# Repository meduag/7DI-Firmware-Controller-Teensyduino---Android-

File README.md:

# 7DI-Firmware-Controller-Teensyduino---Android-
Proyecto de desarrollo de un controlador de un dispositivo de estimulación eléctrica, basado en Android y arduino via Bluetooth

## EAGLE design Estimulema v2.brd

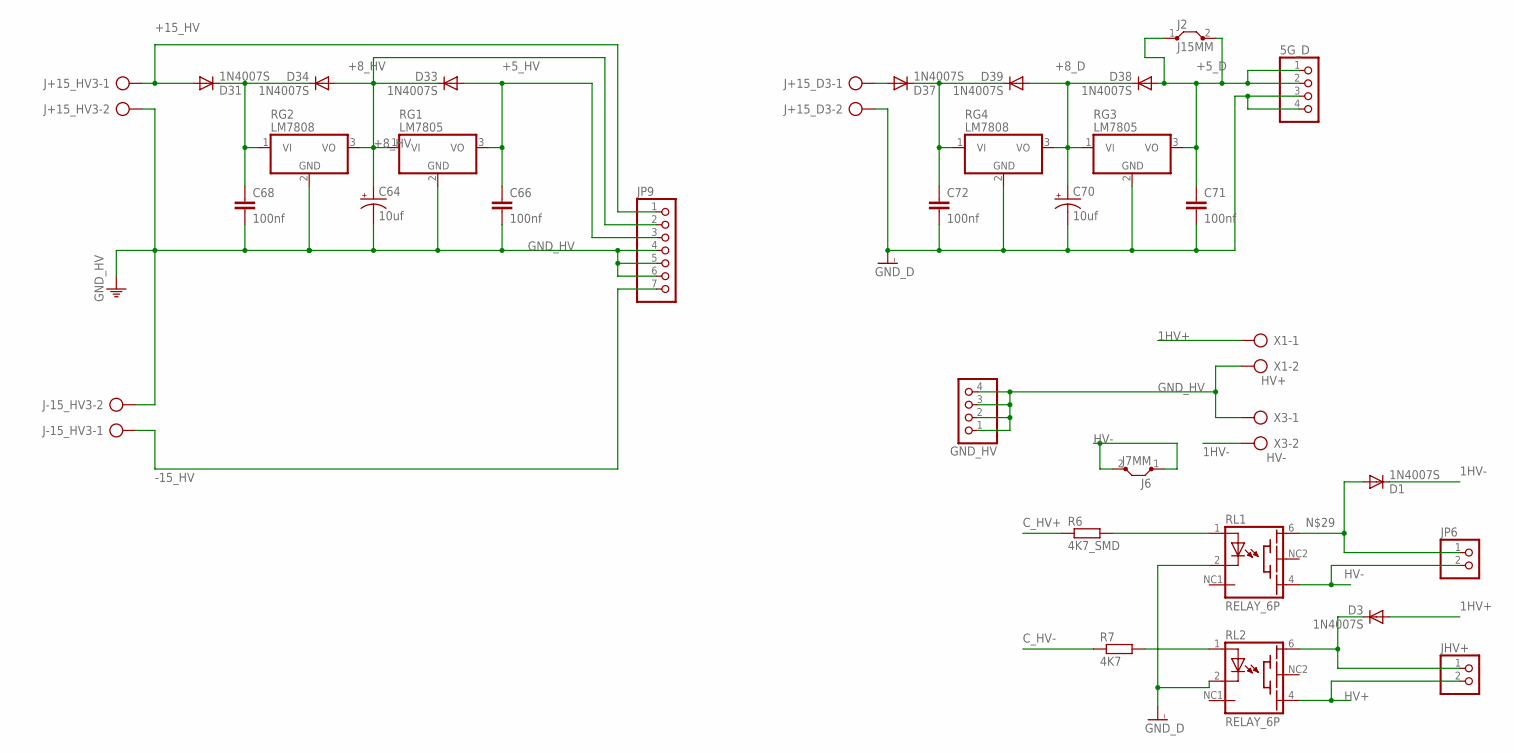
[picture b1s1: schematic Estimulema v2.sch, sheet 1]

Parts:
5G_D: PINHD-1X4; 1X04
C64, C70: 10uf; E2-5
C66, C68, C71, C72: 100nf; C025-024X044
D1, D3, D31, D33, D34, D37, D38, D39: 1N4007S; DIODO4MM
GND_HV: PINHD-1X4; 1X04
J2: J15MM; 15
J6: J7MM; 07
J+15_D3, J+15_HV3: AK300/2
J-15_HV3: AK300/2
JHV+: PINHD-1X2; 1X02
JP6: PINHD-1X2; 1X02
JP9: PINHD-1X7; 1X07
R6: 4K7_SMD; RESISTENCIA_0805
R7: 4K7; RESISTENCIA_0805
RG1, RG3: LM7805; TO220V
RG2, RG4: LM7808; TO220V
RL1, RL2: RELAY_6P; TS210
X1: HV+; AK300/2
X3: HV-; AK300/2

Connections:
1HV+: D3.A, X1.1
1HV-: D1.C, X3.2
+4: D37.A, J+15_D3.1
+5_D: 5G_D.1, 5G_D.2, C71.1, D38.A, J2.1, J2.2, RG3.3 (VO); also elsewhere on the board
+5_HV: C66.1, D33.A, JP9.3, RG1.3 (VO); also elsewhere on the board
+8_D: C70.+, D38.C, D39.A, RG3.1 (VI), RG4.3 (VO)
+8_HV: C64.+, D33.C, D34.A, JP9.2, RG1.1 (VI), RG2.3 (VO)
+15_HV: D31.A, J+15_HV3.1, JP9.1; also elsewhere on the board
-15_HV: J-15_HV3.1, JP9.7; also elsewhere on the board
C_HV+: R6.1; also elsewhere on the board
C_HV-: R7.1; also elsewhere on the board
GND_D: 5G_D.3, 5G_D.4, C70.-, C71.2, C72.2, J+15_D3.2, RG3.2 (GND), RG4.2 (GND), RL1.2 (C), RL2.2 (C); also elsewhere on the board
GND_HV: C64.-, C66.2, C68.2, GND_HV.1, GND_HV.2, GND_HV.3, GND_HV.4, J+15_HV3.2, J-15_HV3.2, JP9.4, JP9.5, JP9.6, RG1.2 (GND), RG2.2 (GND), X1.2, X3.1; also elsewhere on the board
HV+: JHV+.2, RL2.4 (EMI); also elsewhere on the board
HV-: J6.1, J6.2, JP6.2, RL1.4 (EMI); also elsewhere on the board
unnamed: R6.2, RL1.1 (A)
unnamed: R7.2, RL2.1 (A)
unnamed: D1.A, JP6.1, RL1.6 (BAS)
unnamed: D3.C, JHV+.1, RL2.6 (BAS)
unnamed: C68.1, D31.C, D34.C, RG2.1 (VI)
unnamed: C72.1, D37.C, D39.C, RG4.1 (VI)

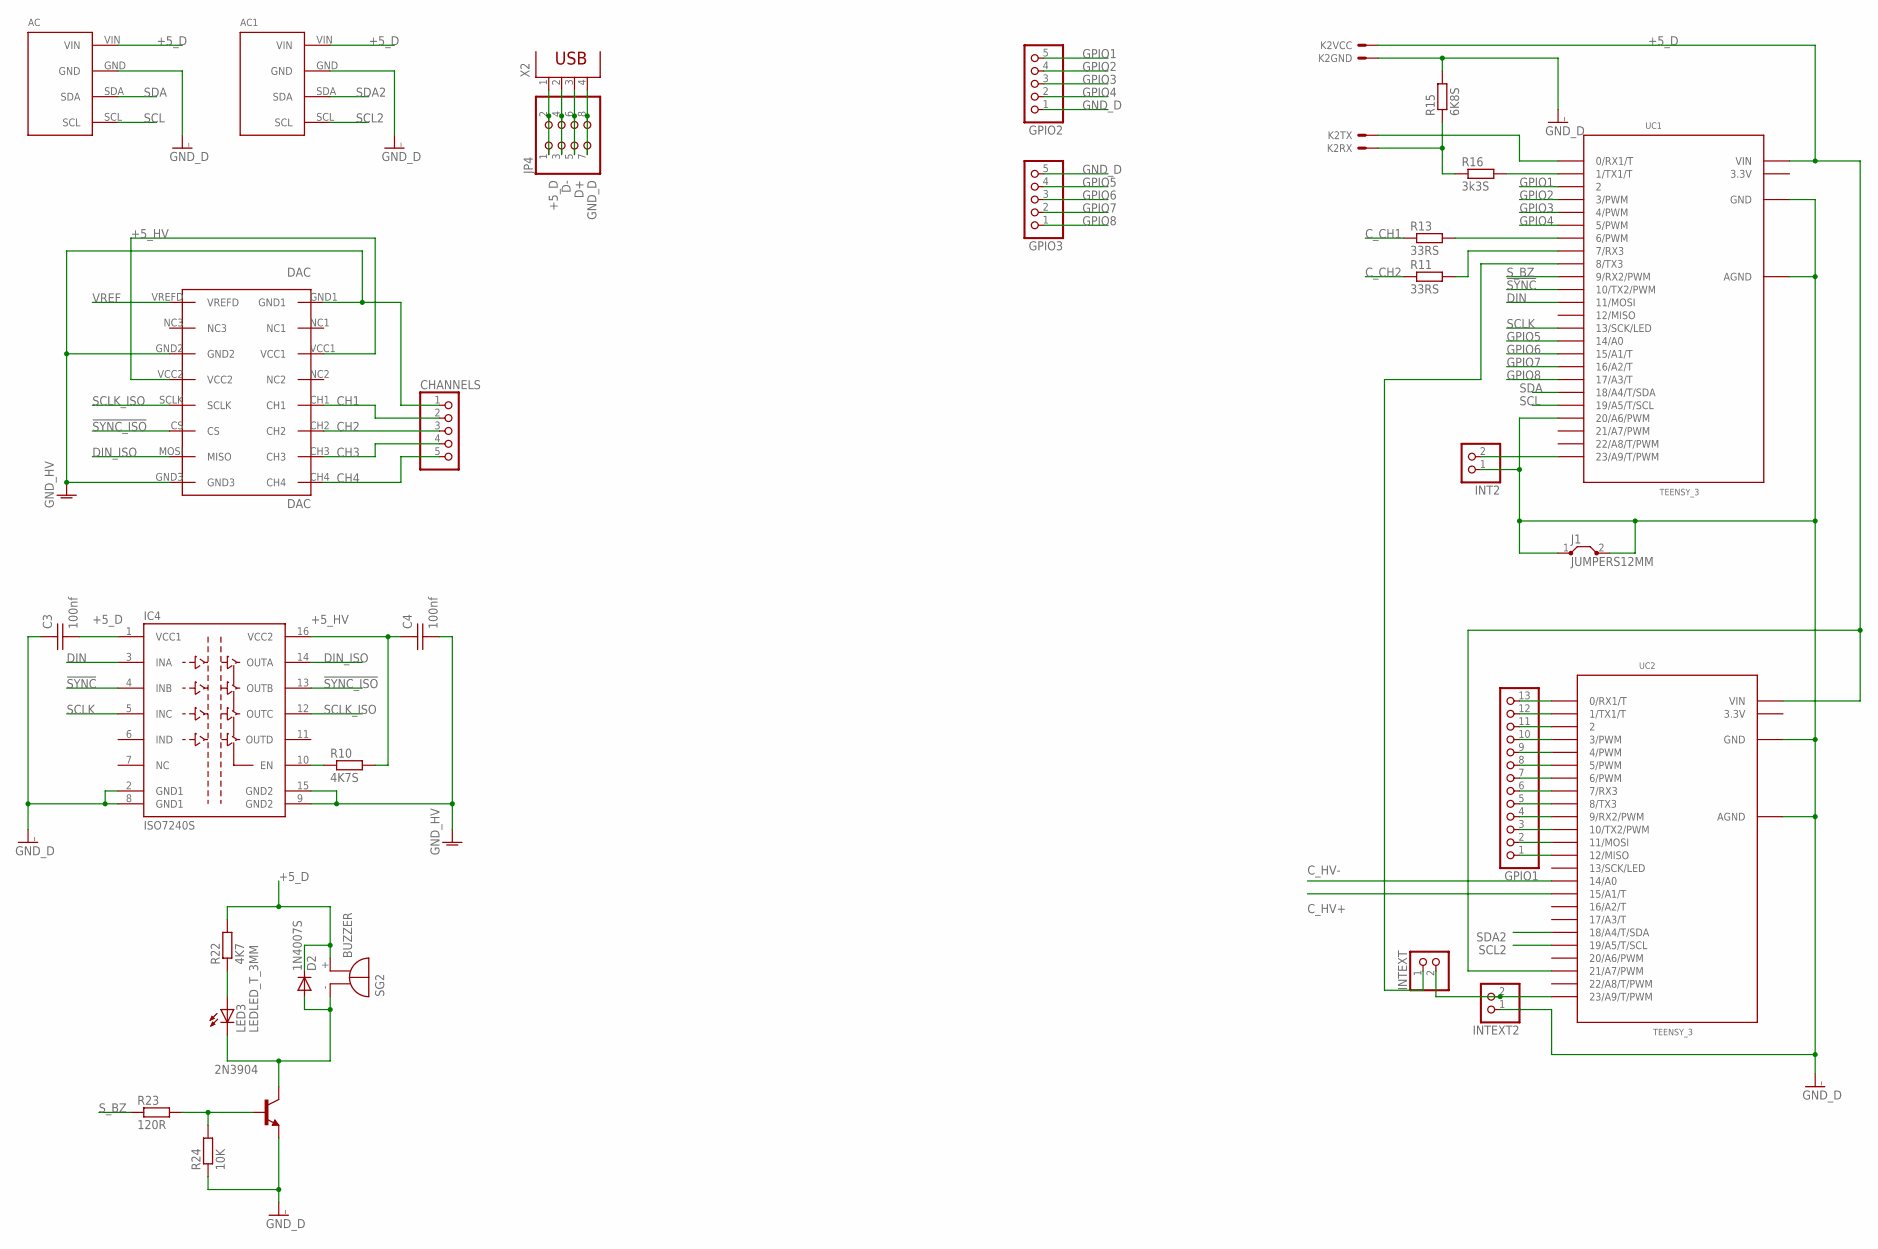
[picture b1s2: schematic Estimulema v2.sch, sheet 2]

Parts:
2N3904: 29-NPN-TO92-EBC; TO92-EBC
AC: CONECTOR_ACELEROMETRO_MPU6050CONECTOR_MPU6050; MPU6050
AC1: MPU6050
C3, C4: 100nf; CAP_CER_SMD-0805
CHANNELS: PINHD-1X5; 1X05
D2: 1N4007S; DIODO4MM
DAC: DAC; DACMOD_P
GPIO1: PINHD-1X13; 1X13
GPIO2, GPIO3: PINHD-1X5; 1X05
IC4: ISO7240S; SO-16DW
INT2: PINHD-1X2; 1X02
INTEXT, INTEXT2: PINHD-1X2; 1X02
J1: JUMPERS12MM; 12
JP4: PINHD-2X4; 2X04
K2: HC-06; CONECTOR_BTHC-06
LED3: LEDLED_T_3MM; LED3MM
R10: 4K7S; RESISTENCIA_0805
R11, R13: 33RS; RESISTENCIA_0805
R15: 6K8S; RESISTENCIA_0805
R16: 3k3S; RESISTENCIA_0805
R22: 4K7; RESISTENCIA_0805
R23: 120R; RESISTENCIA_0805
R24: 10K; RESISTENCIA_0805
SG2: BUZZER
UC1, UC2: TEENSY_3; TEENSY_3.0-3.2_DIL
X2: PN61729

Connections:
3.3V: UC1.3.3V, UC2.3.3V
!SYNC: IC4.4 (INB), UC1.10 (10/TX2/PWM)
!SYNC_ISO: DAC.CS, IC4.13 (OUTB)
+5_D: AC.VIN, AC1.VIN, C3.2, D2.C, IC4.1 (VCC1), JP4.1, JP4.2, K2.1, R22.2, SG2.+ (-), UC1.VIN, UC2.21/A7 (21/A7/PWM), UC2.VIN, X2.1; also elsewhere on the board
+5_HV: C4.1, DAC.VCC1, DAC.VCC2, IC4.16 (VCC2), R10.2; also elsewhere on the board
CH1: CHANNELS.2, DAC.CH1; also elsewhere on the board
CH2: CHANNELS.3, DAC.CH2; also elsewhere on the board
CH3: CHANNELS.4, DAC.CH3
CH4: CHANNELS.5, DAC.CH4
C_CH1: R13.1; also elsewhere on the board
C_CH2: R11.1; also elsewhere on the board
C_HV+: UC2.15/A1 (15/A1/T); also elsewhere on the board
C_HV-: UC2.14/A0; also elsewhere on the board
D+: JP4.5, JP4.6, X2.3
D-: JP4.3, JP4.4, X2.2
DIN: IC4.3 (INA), UC1.11 (11/MOSI)
DIN_ISO: DAC.MOSI (MISO), IC4.14 (OUTA)
GNDI: C3.1, IC4.2 (GND1), IC4.8 (GND1)
GND_D: 2N3904.E, AC.GND, AC1.GND, GPIO2.1, GPIO3.5, INT2.1, INTEXT2.1, J1.1, J1.2, JP4.7, JP4.8, K2.2, R15.2, R24.1, UC1.20/A6 (20/A6/PWM), UC1.AGND, UC1.GND, UC2.AGND, UC2.GND, X2.4; also elsewhere on the board
GND_HV: C4.2, CHANNELS.1, DAC.GND1, DAC.GND2, DAC.GND3, IC4.9 (GND2), IC4.15 (GND2); also elsewhere on the board
GPIO1: GPIO2.5, UC1.2
GPIO2: GPIO2.4, UC1.3 (3/PWM)
GPIO3: GPIO2.3, UC1.4 (4/PWM)
GPIO4: GPIO2.2, UC1.5 (5/PWM)
GPIO5: GPIO3.4, UC1.14/A0
GPIO6: GPIO3.3, UC1.15/A1 (15/A1/T)
GPIO7: GPIO3.2, UC1.16/A2 (16/A2/T)
GPIO8: GPIO3.1, UC1.17/A3 (17/A3/T)
unnamed: INTEXT.2, INTEXT2.2, UC2.23/A9 (23/A9/T/PWM)
unnamed: INTEXT.1, UC1.8 (8/TX3)
unnamed: GPIO1.13, UC2.0 (0/RX1/T)
unnamed: GPIO1.12, UC2.1 (1/TX1/T)
unnamed: GPIO1.11, UC2.2
unnamed: GPIO1.10, UC2.3 (3/PWM)
unnamed: GPIO1.9, UC2.4 (4/PWM)
unnamed: GPIO1.8, UC2.5 (5/PWM)
unnamed: GPIO1.7, UC2.6 (6/PWM)
unnamed: GPIO1.6, UC2.7 (7/RX3)
unnamed: GPIO1.5, UC2.8 (8/TX3)
unnamed: GPIO1.4, UC2.9 (9/RX2/PWM)
unnamed: GPIO1.3, UC2.10 (10/TX2/PWM)
unnamed: GPIO1.2, UC2.11 (11/MOSI)
unnamed: GPIO1.1, UC2.12 (12/MISO)
unnamed: IC4.10 (EN), R10.1
unnamed: R13.2, UC1.6 (6/PWM)
unnamed: R11.2, UC1.7 (7/RX3)
unnamed: K2.4, R15.1, R16.1
unnamed: R16.2, UC1.1 (1/TX1/T)
unnamed: K2.3, UC1.0 (0/RX1/T)
unnamed: LED3.A, R22.1
unnamed: 2N3904.C, D2.A, LED3.K (C), SG2.- (+)
unnamed: 2N3904.B, R23.2, R24.2
unnamed: INT2.2, UC1.23/A9 (23/A9/T/PWM)
SCL: AC.SCL, UC1.19/A5 (19/A5/T/SCL)
SCL2: AC1.SCL, UC2.19/A5 (19/A5/T/SCL)
SCLK: IC4.5 (INC), UC1.13 (13/SCK/LED)
SCLK_ISO: DAC.SCLK, IC4.12 (OUTC)
SDA: AC.SDA, UC1.18/A4 (18/A4/T/SDA)
SDA2: AC1.SDA, UC2.18/A4 (18/A4/T/SDA)
S_BZ: R23.1, UC1.9 (9/RX2/PWM)
VREF: DAC.VREFD; also elsewhere on the board

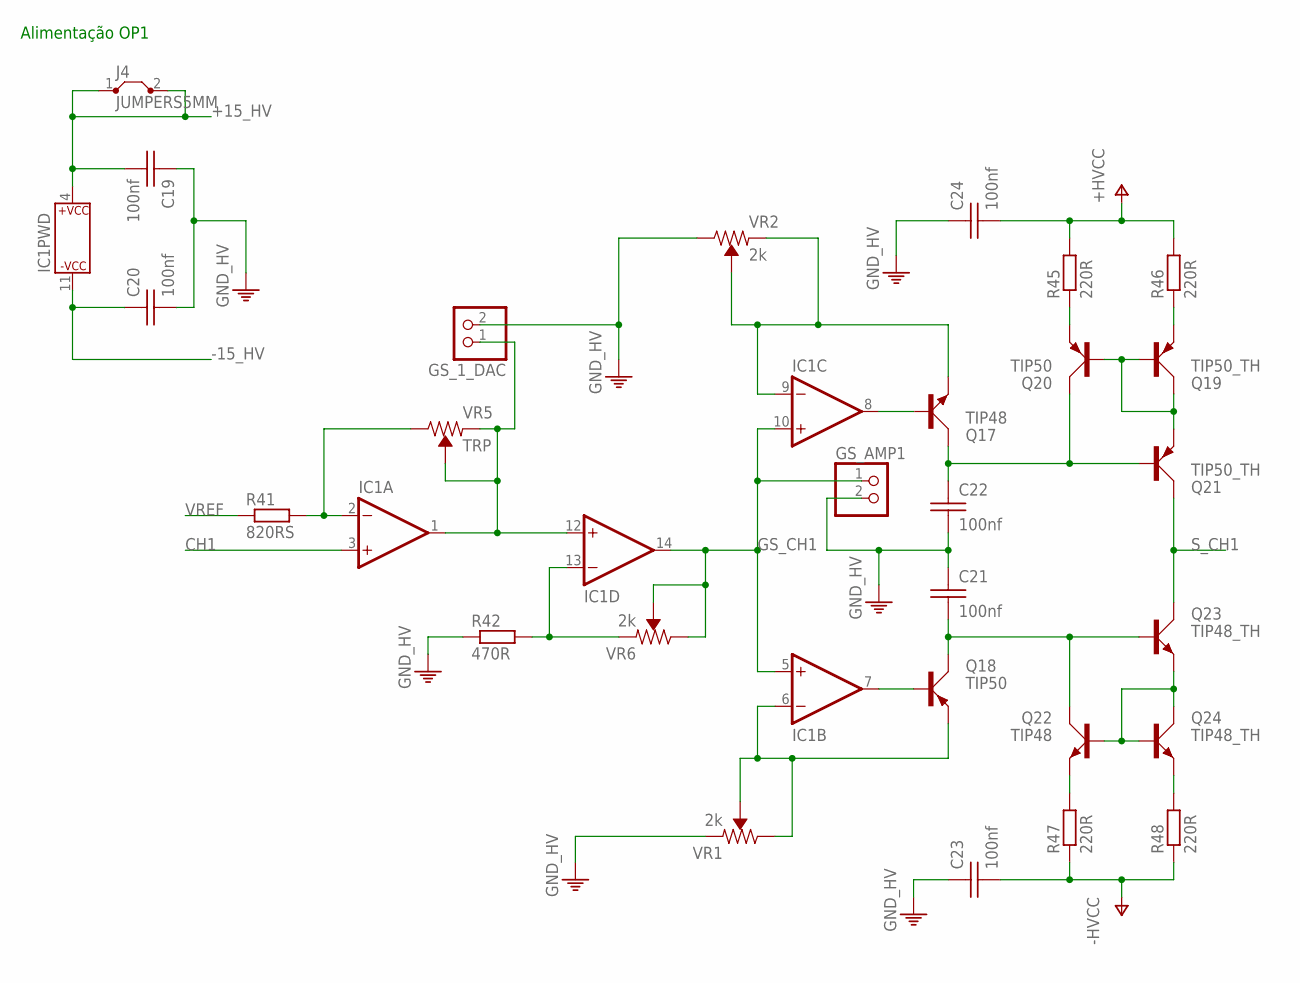
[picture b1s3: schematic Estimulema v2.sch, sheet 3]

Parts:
C19, C20: 100nf; CAP_CER_SMD-0805
C21, C22: 100nf; CAP_CER_2,54-5X5
C23, C24: 100nf; CAP_CER_16X7
GS_1_DAC: PINHD-1X2; 1X02
GS_AMP1: PINHD-1X2; 1X02
IC1: TL084; DIL14
J4: JUMPERS5MM; 05
Q17, Q22: TIP48; TO220
Q18, Q20: TIP50; TO220
Q19, Q21: TIP50_TH; TO220
Q23, Q24: TIP48_TH; TO220
R41: 820RS; RESISTENCIA_0805
R42: 470R; RESISTENCIA_0805
R45, R46, R47, R48: 220R; 0204V
VR1, VR2, VR6: 2k; TRIMPOT-PTH-3386U
VR5: TRP; TRIMPOT-PTH-3386U

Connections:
+15_HV: C19.2, IC1.4 (P$V+), J4.1, J4.2; also elsewhere on the board
-15_HV: C20.1, IC1.11 (P$V-); also elsewhere on the board
CH1: IC1.3 (+IN); also elsewhere on the board
GND_HV: C19.1, C20.2, C21.1, C22.2, C23.1, C24.1, GS_1_DAC.2, GS_AMP1.2, R42.1, VR1.1 (CCW), VR2.3 (CW); also elsewhere on the board
GS_CH1: GS_AMP1.1, IC1.5 (+IN), IC1.10 (+IN), IC1.14 (OUT), VR6.2 (WIPER), VR6.3 (CW)
HV+: C24.2, R45.2, R46.2; also elsewhere on the board
HV-: C23.2, R47.1, R48.1; also elsewhere on the board
unnamed: IC1.2 (-IN), R41.2, VR5.3 (CW)
unnamed: GS_1_DAC.1, IC1.1 (OUT), IC1.12 (+IN), VR5.1 (CCW), VR5.2 (WIPER)
unnamed: IC1.13 (-IN), R42.2, VR6.1 (CCW)
unnamed: IC1.9 (-IN), Q17.E, VR2.1 (CCW), VR2.2 (WIPER)
unnamed: IC1.6 (-IN), Q18.E, VR1.2 (WIPER), VR1.3 (CW)
unnamed: C21.2, Q18.C, Q22.C, Q23.B
unnamed: C22.1, Q17.C, Q20.C, Q21.B
unnamed: Q20.E, R45.1
unnamed: Q19.E, R46.1
unnamed: Q19.B, Q19.C, Q20.B, Q21.E
unnamed: Q22.B, Q23.E, Q24.B, Q24.C
unnamed: Q22.E, R47.2
unnamed: Q24.E, R48.2
unnamed: IC1.8 (OUT), Q17.B
unnamed: IC1.7 (OUT), Q18.B
S_CH1: Q21.C, Q23.C; also elsewhere on the board
VREF: R41.1; also elsewhere on the board

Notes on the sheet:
Alimentação OP1

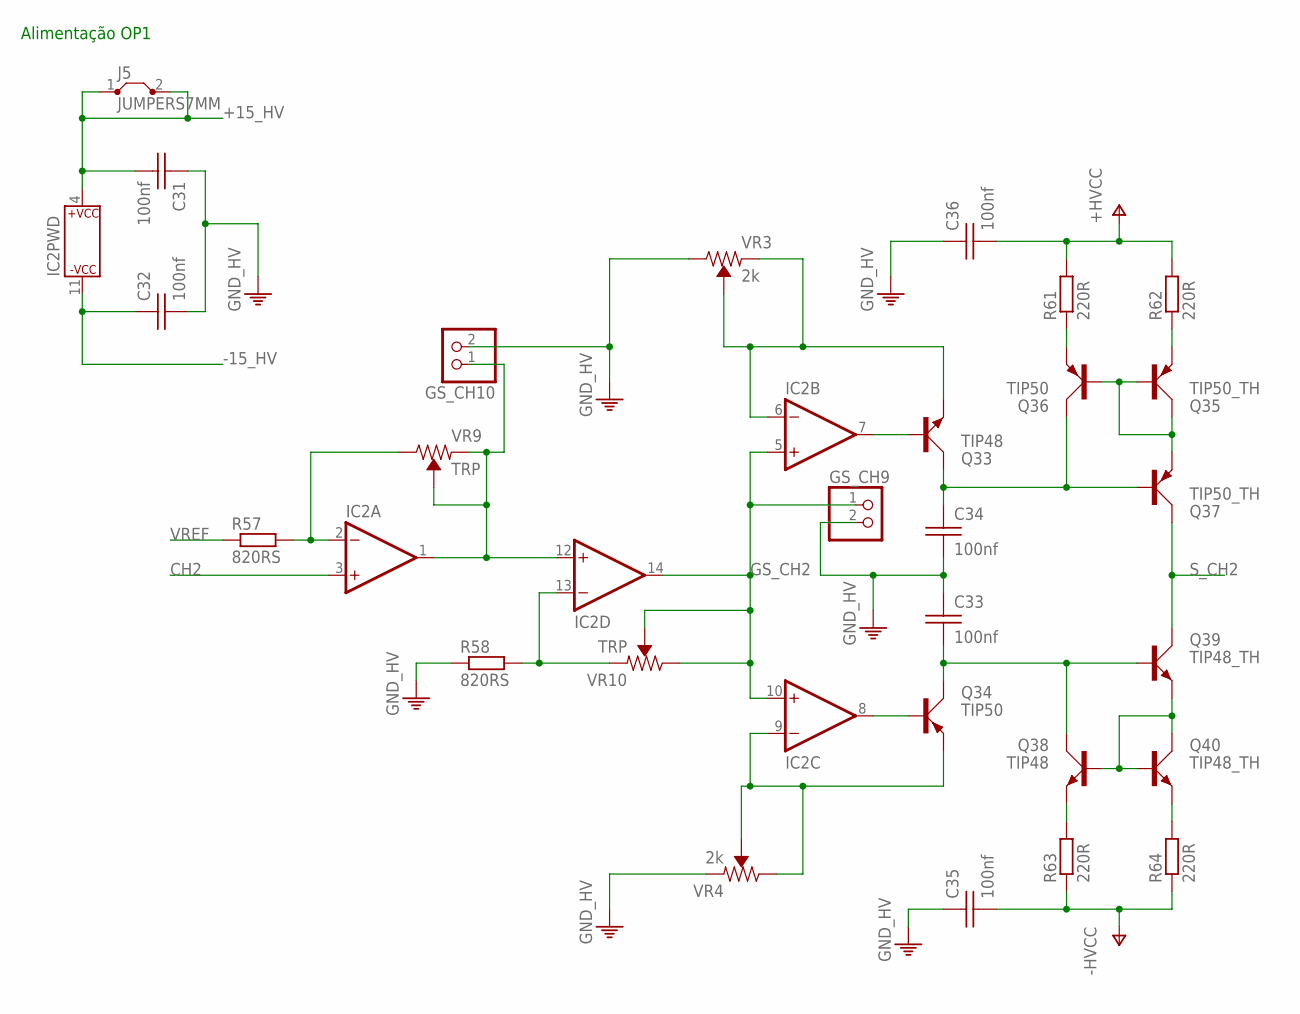
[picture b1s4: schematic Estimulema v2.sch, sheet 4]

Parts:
C31, C32: 100nf; CAP_CER_SMD-0805
C33, C34: 100nf; CAP_CER_2,54-5X5
C35, C36: 100nf; CAP_CER_16X7
GS_CH9, GS_CH10: PINHD-1X2; 1X02
IC2: TL084; DIL14
J5: JUMPERS7MM; 07
Q33, Q38: TIP48; TO220
Q34, Q36: TIP50; TO220
Q35, Q37: TIP50_TH; TO220
Q39, Q40: TIP48_TH; TO220
R57, R58: 820RS; RESISTENCIA_0805
R61, R62, R63, R64: 220R; 0204V
VR3, VR4: 2k; TRIMPOT-PTH-3386U
VR9, VR10: TRP; TRIMPOT-PTH-3386U

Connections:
+15_HV: C31.2, IC2.4 (P$V+), J5.1, J5.2; also elsewhere on the board
-15_HV: C32.1, IC2.11 (P$V-); also elsewhere on the board
CH2: IC2.3 (+IN); also elsewhere on the board
GND_HV: C31.1, C32.2, C33.1, C34.2, C35.1, C36.1, GS_CH9.2, GS_CH10.2, R58.1, VR3.3 (CW), VR4.1 (CCW); also elsewhere on the board
GS_CH2: GS_CH9.1, IC2.5 (+IN), IC2.10 (+IN), IC2.14 (OUT), VR10.2 (WIPER), VR10.3 (CW)
HV+: C36.2, R61.2, R62.2; also elsewhere on the board
HV-: C35.2, R63.1, R64.1; also elsewhere on the board
unnamed: IC2.2 (-IN), R57.2, VR9.3 (CW)
unnamed: GS_CH10.1, IC2.1 (OUT), IC2.12 (+IN), VR9.1 (CCW), VR9.2 (WIPER)
unnamed: IC2.13 (-IN), R58.2, VR10.1 (CCW)
unnamed: IC2.6 (-IN), Q33.E, VR3.1 (CCW), VR3.2 (WIPER)
unnamed: IC2.9 (-IN), Q34.E, VR4.2 (WIPER), VR4.3 (CW)
unnamed: C33.2, Q34.C, Q38.C, Q39.B
unnamed: C34.1, Q33.C, Q36.C, Q37.B
unnamed: Q36.E, R61.1
unnamed: Q35.E, R62.1
unnamed: Q35.B, Q35.C, Q36.B, Q37.E
unnamed: Q38.B, Q39.E, Q40.B, Q40.C
unnamed: Q38.E, R63.2
unnamed: Q40.E, R64.2
unnamed: IC2.7 (OUT), Q33.B
unnamed: IC2.8 (OUT), Q34.B
S_CH2: Q37.C, Q39.C; also elsewhere on the board
VREF: R57.1; also elsewhere on the board

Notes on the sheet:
Alimentação OP1

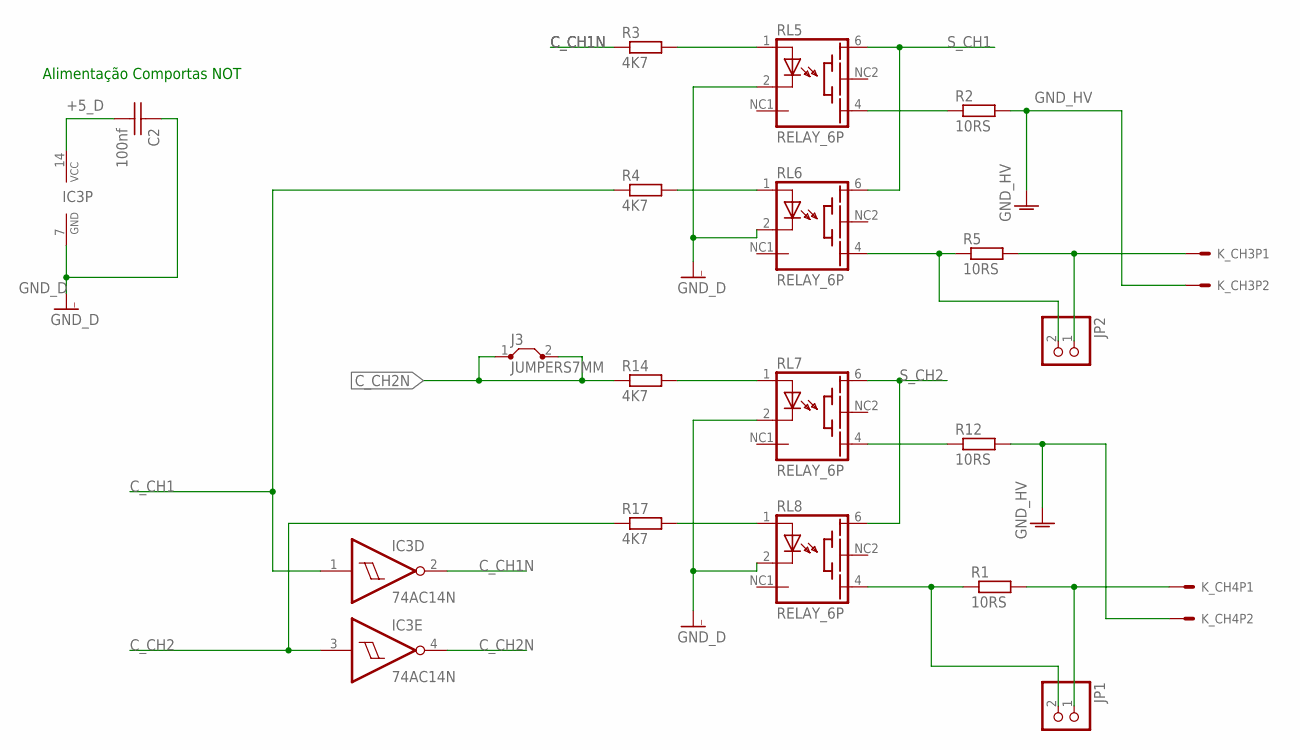
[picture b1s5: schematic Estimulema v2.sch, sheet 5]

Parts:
C2: 100nf; CAP_CER_SMD-0805
IC3: 74AC14N; DIL14
J3: JUMPERS7MM; 07
JP1, JP2: PINHD-1X2; 1X02
K_CH3, K_CH4: CONECTOR_5.08; CONECTOR_X2_5.08
R1, R5: 10RS; 0204/5
R2, R12: 10RS; 0617V
R3, R4, R14, R17: 4K7; RESISTENCIA_0805
RL5, RL6, RL7, RL8: RELAY_6P; TS210

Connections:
+5_D: C2.2, IC3.14 (VCC); also elsewhere on the board
C_CH1: IC3.1 (I), R4.1; also elsewhere on the board
C_CH1N: IC3.2 (O), R3.1
C_CH2: IC3.3 (I), R17.1; also elsewhere on the board
C_CH2N: IC3.4 (O), J3.1, J3.2, R14.1
GND_D: C2.1, IC3.7 (GND), RL5.2 (C), RL6.2 (C), RL7.2 (C), RL8.2 (C); also elsewhere on the board
GND_HV: K_CH3.2, K_CH4.2, R2.2, R12.2; also elsewhere on the board
unnamed: R3.2, RL5.1 (A)
unnamed: R4.2, RL6.1 (A)
unnamed: R2.1, RL5.4 (EMI)
unnamed: JP2.2, R5.1, RL6.4 (EMI)
unnamed: R14.2, RL7.1 (A)
unnamed: R17.2, RL8.1 (A)
unnamed: R12.1, RL7.4 (EMI)
unnamed: JP2.1, K_CH3.1, R5.2
unnamed: JP1.1, K_CH4.1, R1.2
unnamed: JP1.2, R1.1, RL8.4 (EMI)
S_CH1: RL5.6 (BAS), RL6.6 (BAS); also elsewhere on the board
S_CH2: RL7.6 (BAS), RL8.6 (BAS); also elsewhere on the board

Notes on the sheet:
Alimentação Comportas NOT

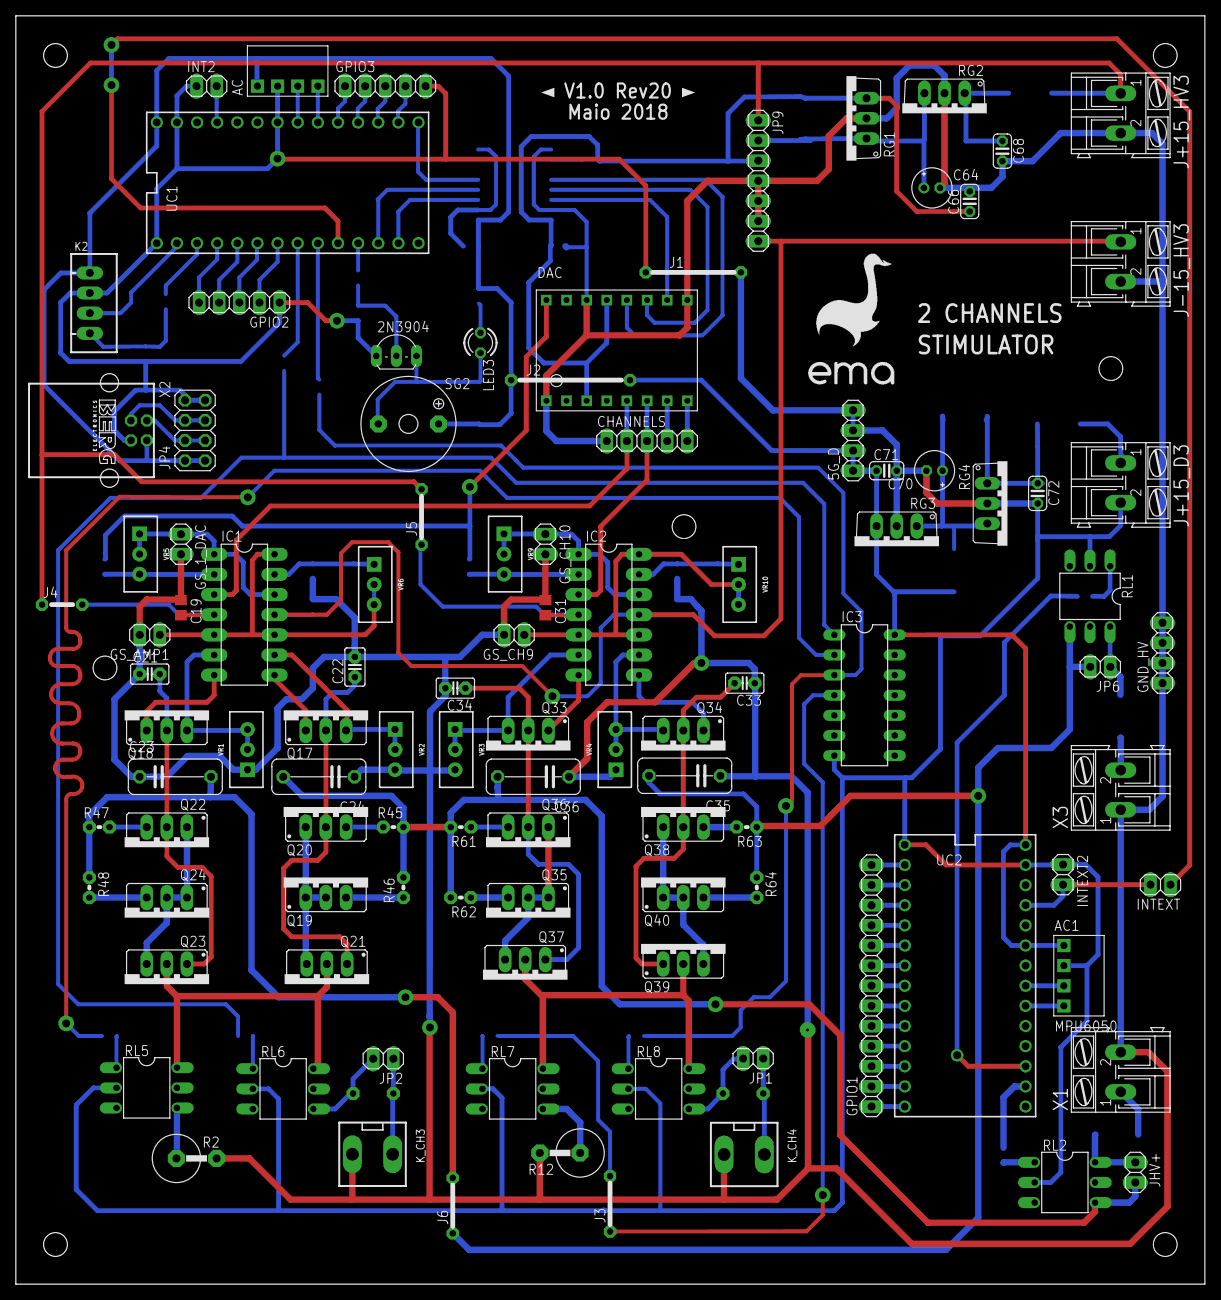
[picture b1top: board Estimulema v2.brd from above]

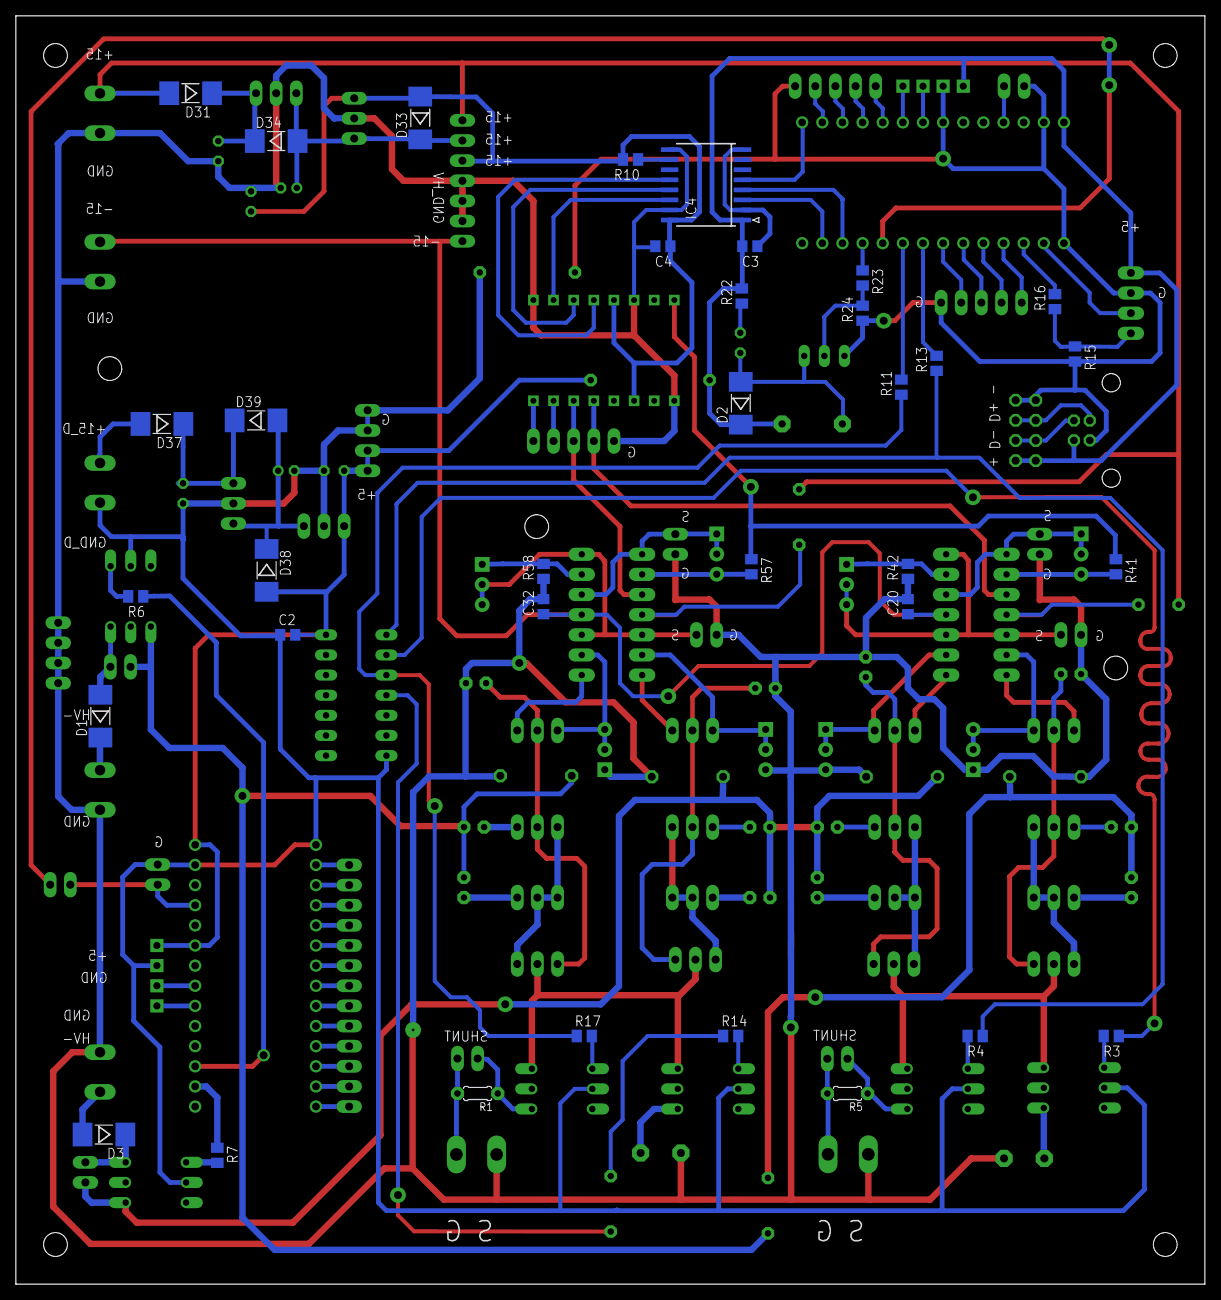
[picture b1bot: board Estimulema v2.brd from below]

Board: 2 copper layers, 150.0 x 160.0 mm, 140 parts (35 on the bottom side), 122 nets.

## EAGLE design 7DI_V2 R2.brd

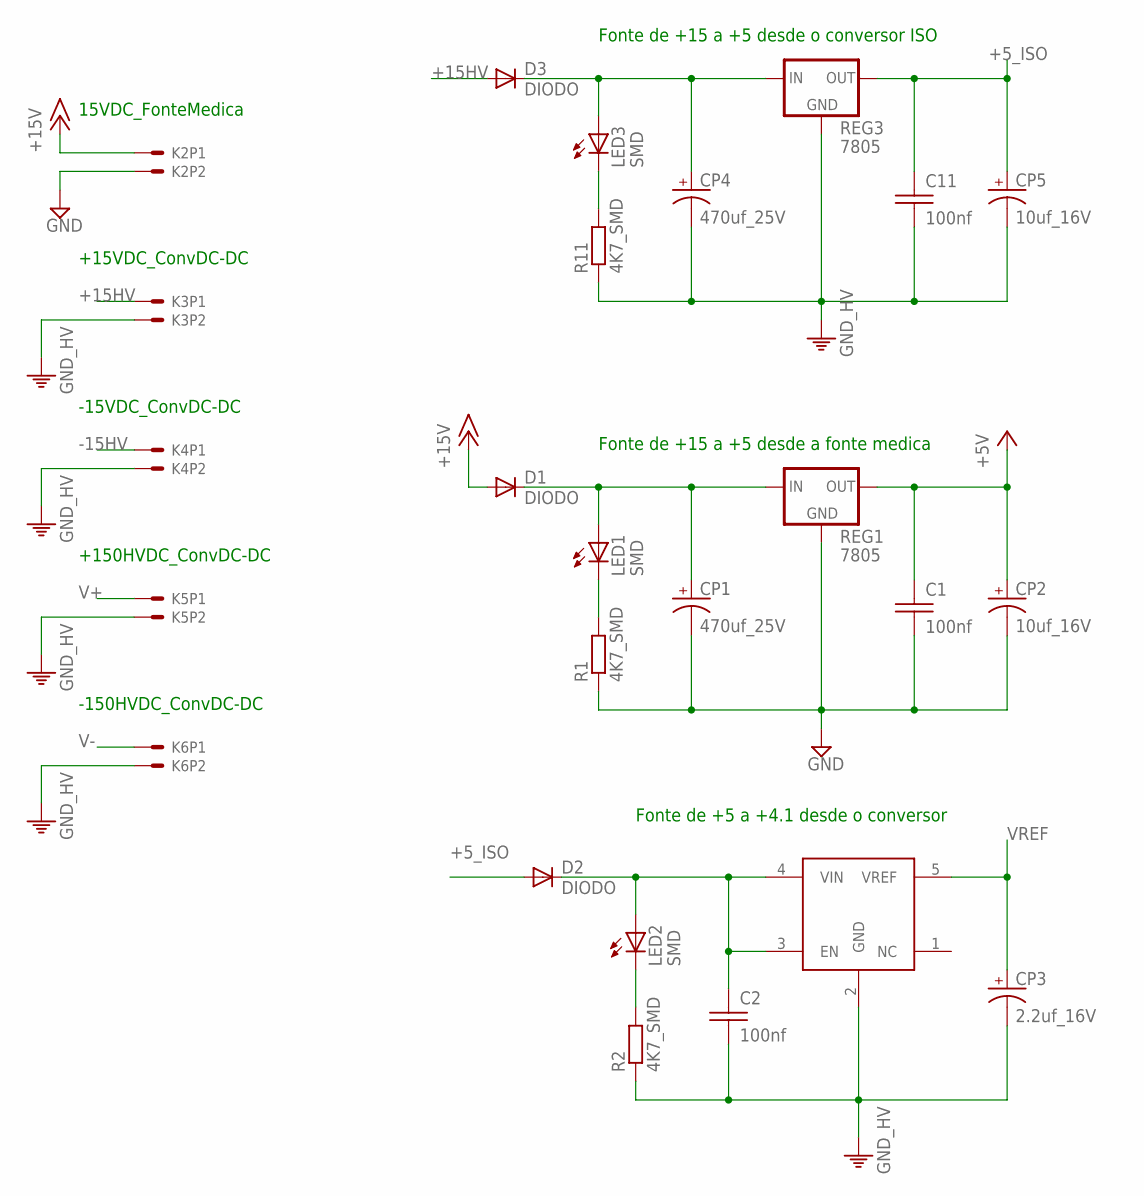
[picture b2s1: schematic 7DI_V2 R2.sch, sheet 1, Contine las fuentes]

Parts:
C1, C11: 100nf; CAP_CER_5,08-024X044
C2: 100nf; CAP_CER_SMD-0805
CP1, CP4: 470uf_25V; CAP_T_3,5-D8
CP2, CP5: 10uf_16V; CAP_T_2,5-D5
CP3: 2.2uf_16V; 153CLV-0605
D1, D2, D3: DIODO; D-5
K2: CONECTOR_5.08; CONECTOR_X2_5.08
K3, K4, K5, K6: vcc; CONECTOR_X2_5.08
LED1, LED2, LED3: SMD; LED_0805
R1, R2, R11: 4K7_SMD; RESISTENCIA_0805
REG1, REG3: 7805; 78XXS
REG2: lm4132_4.1; SOT23

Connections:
+5V: C1.1, CP2.+, REG1.OUT; also elsewhere on the board
+5_ISO: C11.1, CP5.+, D2.A, REG3.OUT; also elsewhere on the board
+15HV: D3.A, K3.1; also elsewhere on the board
+15V: D1.A, K2.1
-15HV: K4.1; also elsewhere on the board
GND: C1.2, CP1.-, CP2.-, K2.2, R1.1, REG1.GND; also elsewhere on the board
unnamed: CP1.+, D1.C, LED1.A, REG1.IN
unnamed: LED1.C, R1.2
unnamed: C2.1, D2.C, LED2.A, REG2.3 (EN), REG2.4 (VIN)
unnamed: LED2.C, R2.2
unnamed: CP4.+, D3.C, LED3.A, REG3.IN
unnamed: LED3.C, R11.2
PE: C2.2, C11.2, CP3.-, CP4.-, CP5.-, K3.2, K4.2, K5.2, K6.2, R2.1, R11.1, REG2.2 (GND), REG3.GND; also elsewhere on the board
V+: K5.1; also elsewhere on the board
V-: K6.1; also elsewhere on the board
VREF: CP3.+, REG2.5 (VREF); also elsewhere on the board

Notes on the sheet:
15VDC_FonteMedica
+15VDC_ConvDC-DC
-15VDC_ConvDC-DC
+150HVDC_ConvDC-DC
-150HVDC_ConvDC-DC
Fonte de +15 a +5 desde o conversor ISO
Fonte de +15 a +5 desde a fonte medica
Fonte de +5 a +4.1 desde o conversor

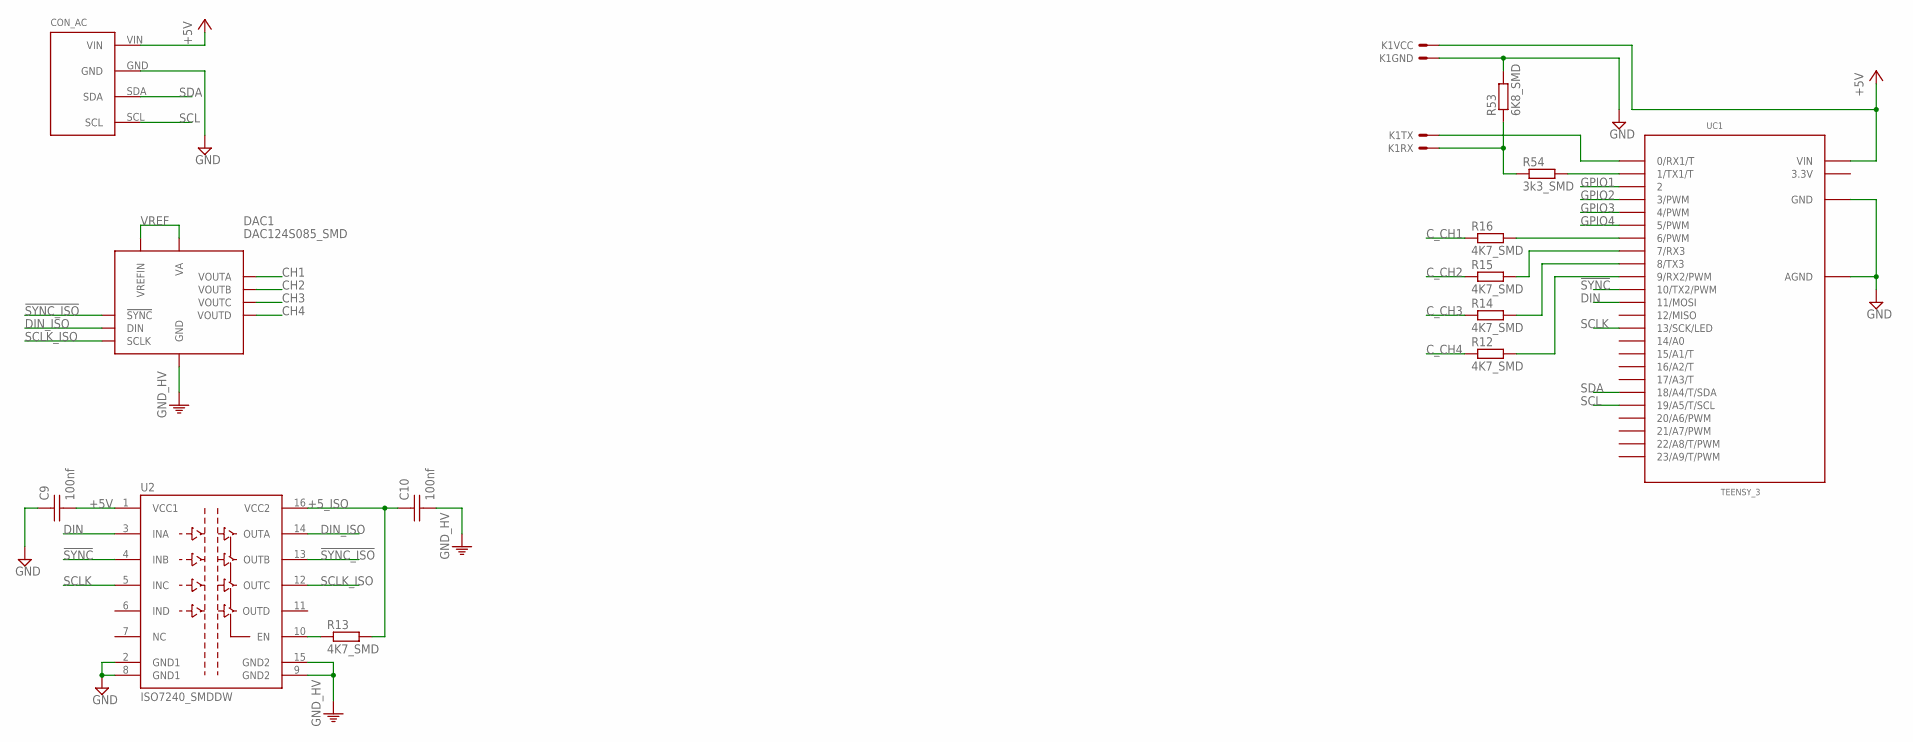
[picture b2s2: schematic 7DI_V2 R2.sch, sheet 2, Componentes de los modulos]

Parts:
C9, C10: 100nf; CAP_CER_SMD-0805
CON_AC: CON_MPU6050; MPU6050
DAC1: DAC124S085_SMD; DAC_SO10
K1: CONECTOR_BTHC-06HC-06; CONECTOR_BTHC-06
R12, R13, R14, R15, R16: 4K7_SMD; RESISTENCIA_0805
R53: 6K8_SMD; RESISTENCIA_0805
R54: 3k3_SMD; RESISTENCIA_0805
U2: ISO7240_SMDDW; SO-16DW
UC1: TEENSY_3; TEENSY_3.0-3.2_DIL

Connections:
3.3V: UC1.3.3V
!SYNC: U2.4 (INB), UC1.10 (10/TX2/PWM)
!SYNC_ISO: DAC1.9 (!SYNC!), U2.13 (OUTB)
+5V: C9.2, CON_AC.VIN, K1.1, U2.1 (VCC1), UC1.VIN; also elsewhere on the board
+5_ISO: C10.1, R13.2, U2.16 (VCC2); also elsewhere on the board
CH1: DAC1.2 (VOUTA); also elsewhere on the board
CH2: DAC1.3 (VOUTB); also elsewhere on the board
CH3: DAC1.4 (VOUTC); also elsewhere on the board
CH4: DAC1.5 (VOUTD); also elsewhere on the board
C_CH1: R16.1; also elsewhere on the board
C_CH2: R15.1; also elsewhere on the board
C_CH3: R14.1; also elsewhere on the board
C_CH4: R12.1; also elsewhere on the board
DIN: U2.3 (INA), UC1.11 (11/MOSI)
DIN_ISO: DAC1.8 (DIN), U2.14 (OUTA)
GND: C9.1, CON_AC.GND, K1.2, R53.2, U2.2 (GND1), U2.8 (GND1), UC1.AGND, UC1.GND; also elsewhere on the board
GPIO1: UC1.2
GPIO2: UC1.3 (3/PWM)
GPIO3: UC1.4 (4/PWM)
GPIO4: UC1.5 (5/PWM)
unnamed: K1.4, R53.1, R54.1
unnamed: R54.2, UC1.1 (1/TX1/T)
unnamed: R13.1, U2.10 (EN)
unnamed: R16.2, UC1.6 (6/PWM)
unnamed: R15.2, UC1.7 (7/RX3)
unnamed: R14.2, UC1.8 (8/TX3)
unnamed: R12.2, UC1.9 (9/RX2/PWM)
unnamed: K1.3, UC1.0 (0/RX1/T)
PE: C10.2, DAC1.6 (GND), U2.9 (GND2), U2.15 (GND2); also elsewhere on the board
SCL: CON_AC.SCL, UC1.19/A5 (19/A5/T/SCL)
SCLK: U2.5 (INC), UC1.13 (13/SCK/LED)
SCLK_ISO: DAC1.10 (SCLK), U2.12 (OUTC)
SDA: CON_AC.SDA, UC1.18/A4 (18/A4/T/SDA)
VREF: DAC1.1 (VA), DAC1.7 (VREFIN); also elsewhere on the board

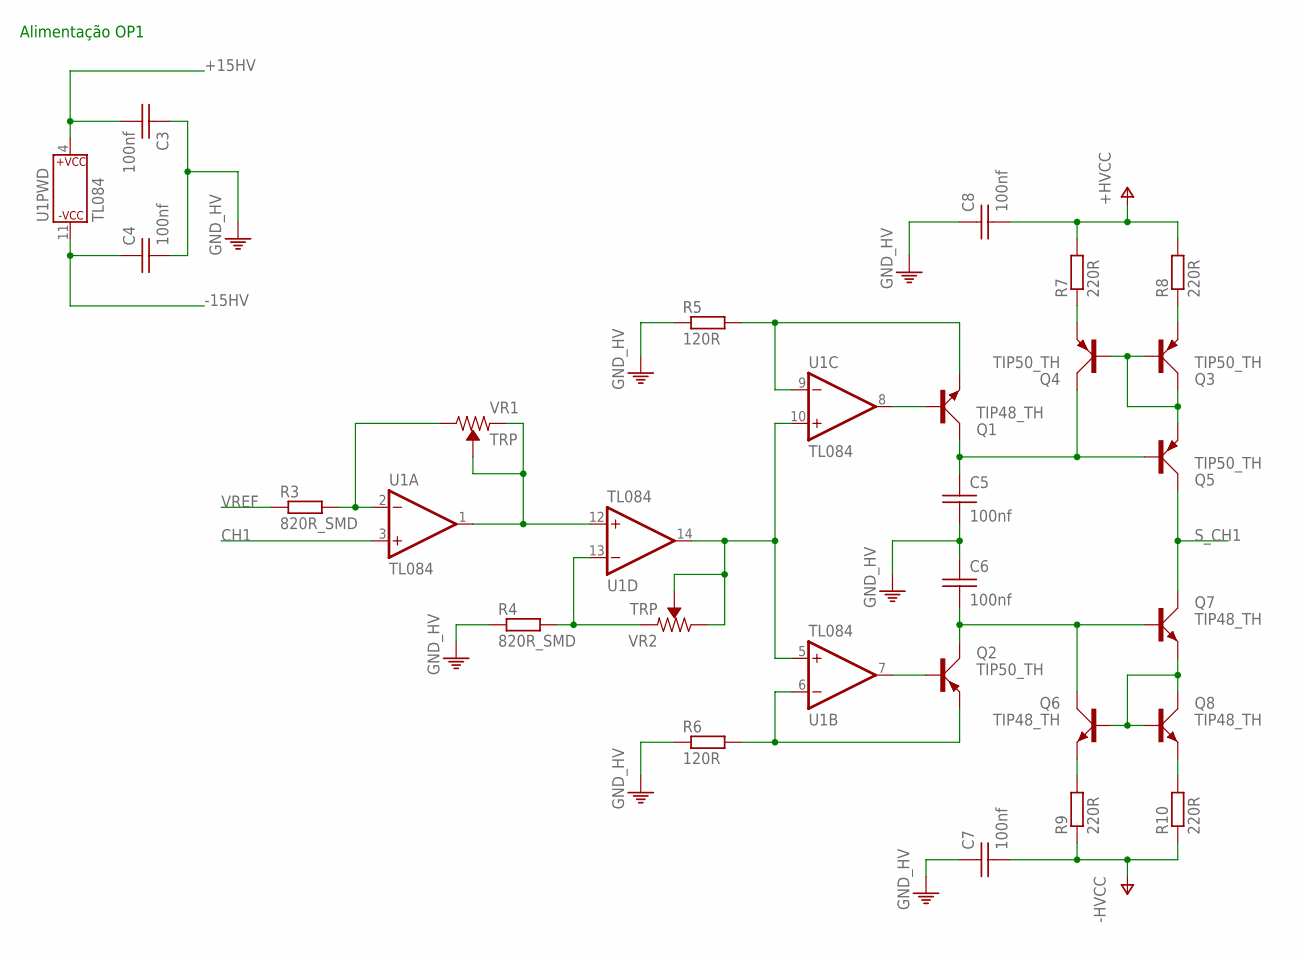
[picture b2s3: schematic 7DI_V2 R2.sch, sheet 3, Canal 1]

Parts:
C3, C4: 100nf; CAP_CER_SMD-0805
C5, C6: 100nf; CAP_CER_2,54-5X5
C7, C8: 100nf; CAP_CER_16X7
Q1, Q6, Q7, Q8: TIP48_TH; TO220
Q2, Q3, Q4, Q5: TIP50_TH; TO220
R3, R4: 820R_SMD; RESISTENCIA_0805
R5, R6: 120R; 0204V
R7, R8, R9, R10: 220R; 0204V
U1: TL084; SO14OP
VR1, VR2: TRP; TRIMPOT-PTH-3386U

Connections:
+15HV: C3.2, U1.4 (P$V+); also elsewhere on the board
-15HV: C4.1, U1.11 (P$V-); also elsewhere on the board
CH1: U1.3 (+IN); also elsewhere on the board
GS_CH1: U1.5 (+IN), U1.10 (+IN), U1.14 (OUT), VR2.2 (WIPER), VR2.3 (CW); also elsewhere on the board
unnamed: R3.2, U1.2 (-IN), VR1.3 (CW)
unnamed: Q1.B, U1.8 (OUT)
unnamed: U1.1 (OUT), U1.12 (+IN), VR1.1 (CCW), VR1.2 (WIPER)
unnamed: Q1.E, R5.2, U1.9 (-IN)
unnamed: Q2.B, U1.7 (OUT)
unnamed: R4.2, U1.13 (-IN), VR2.1 (CCW)
unnamed: Q2.E, R6.2, U1.6 (-IN)
unnamed: C6.2, Q2.C, Q6.C, Q7.B
unnamed: C5.1, Q1.C, Q4.C, Q5.B
unnamed: Q4.E, R7.1
unnamed: Q3.E, R8.1
unnamed: Q3.B, Q3.C, Q4.B, Q5.E
unnamed: Q6.B, Q7.E, Q8.B, Q8.C
unnamed: Q6.E, R9.2
unnamed: Q8.E, R10.2
PE: C3.1, C4.2, C5.2, C6.1, C7.1, C8.1, R4.1, R5.1, R6.1; also elsewhere on the board
S_CH1: Q5.C, Q7.C; also elsewhere on the board
V+: C8.2, R7.2, R8.2; also elsewhere on the board
V-: C7.2, R9.1, R10.1; also elsewhere on the board
VREF: R3.1; also elsewhere on the board

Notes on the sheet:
Alimentação OP1
